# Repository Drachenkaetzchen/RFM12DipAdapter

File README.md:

Simple RFM12 DIP module (RM2) to RM2.5 Adapter

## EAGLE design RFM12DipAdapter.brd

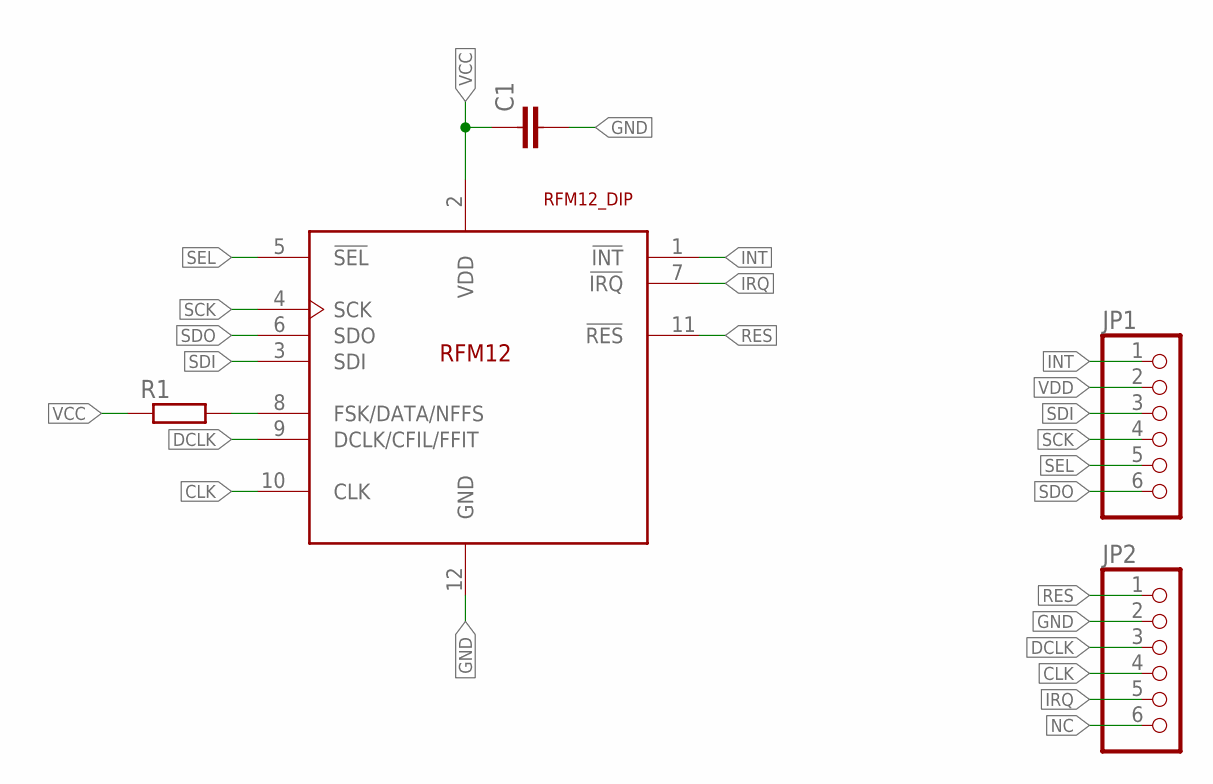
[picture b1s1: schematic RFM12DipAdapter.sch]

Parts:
C1: C-EUC0805; C0805
JP1, JP2: PINHD-1X6; 1X06
R1: R-EU_R1206; R1206
U$1: RFM12_DIP; DIL-2MM-2X06

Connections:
CLK: JP2.4, U$1.10 (CLK)
DCLK: JP2.3, U$1.9 (DCLK/CFIL/FFIT)
GND: C1.2, JP2.2, U$1.12 (GND)
INT: JP1.1, U$1.1 (!INT)
IRQ: JP2.5, U$1.7 (!IRQ)
unnamed: R1.2, U$1.8 (FSK/DATA/NFFS)
NC: JP2.6
RES: JP2.1, U$1.11 (!RES)
SCK: JP1.4, U$1.4 (SCK)
SDI: JP1.3, U$1.3 (SDI)
SDO: JP1.6, U$1.6 (SDO)
SEL: JP1.5, U$1.5 (!SEL)
VCC: C1.1, R1.1, U$1.2 (VDD)
VDD: JP1.2

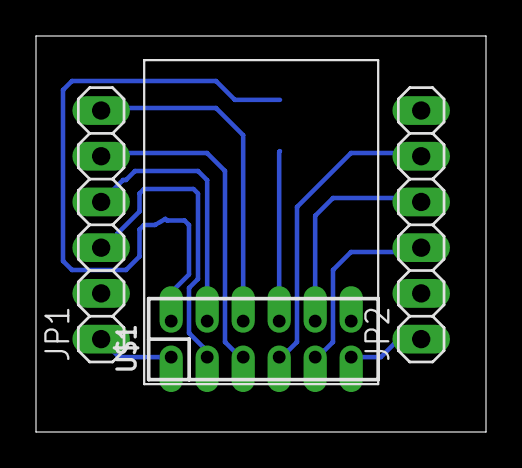
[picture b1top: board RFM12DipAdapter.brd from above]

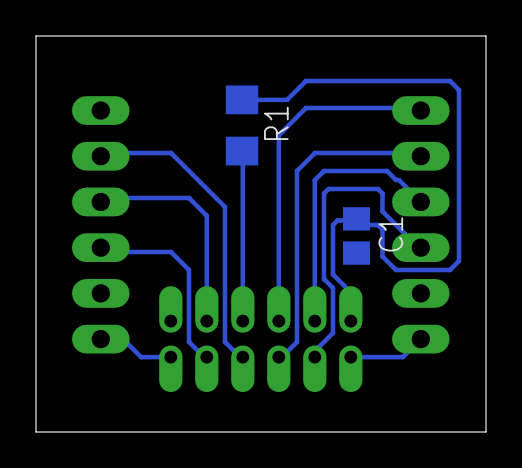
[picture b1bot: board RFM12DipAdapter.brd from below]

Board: 2 copper layers, 25.0 x 22.0 mm, 5 parts (2 on the bottom side), 12 nets.

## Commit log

2013-11-12 Forgot VCC line
